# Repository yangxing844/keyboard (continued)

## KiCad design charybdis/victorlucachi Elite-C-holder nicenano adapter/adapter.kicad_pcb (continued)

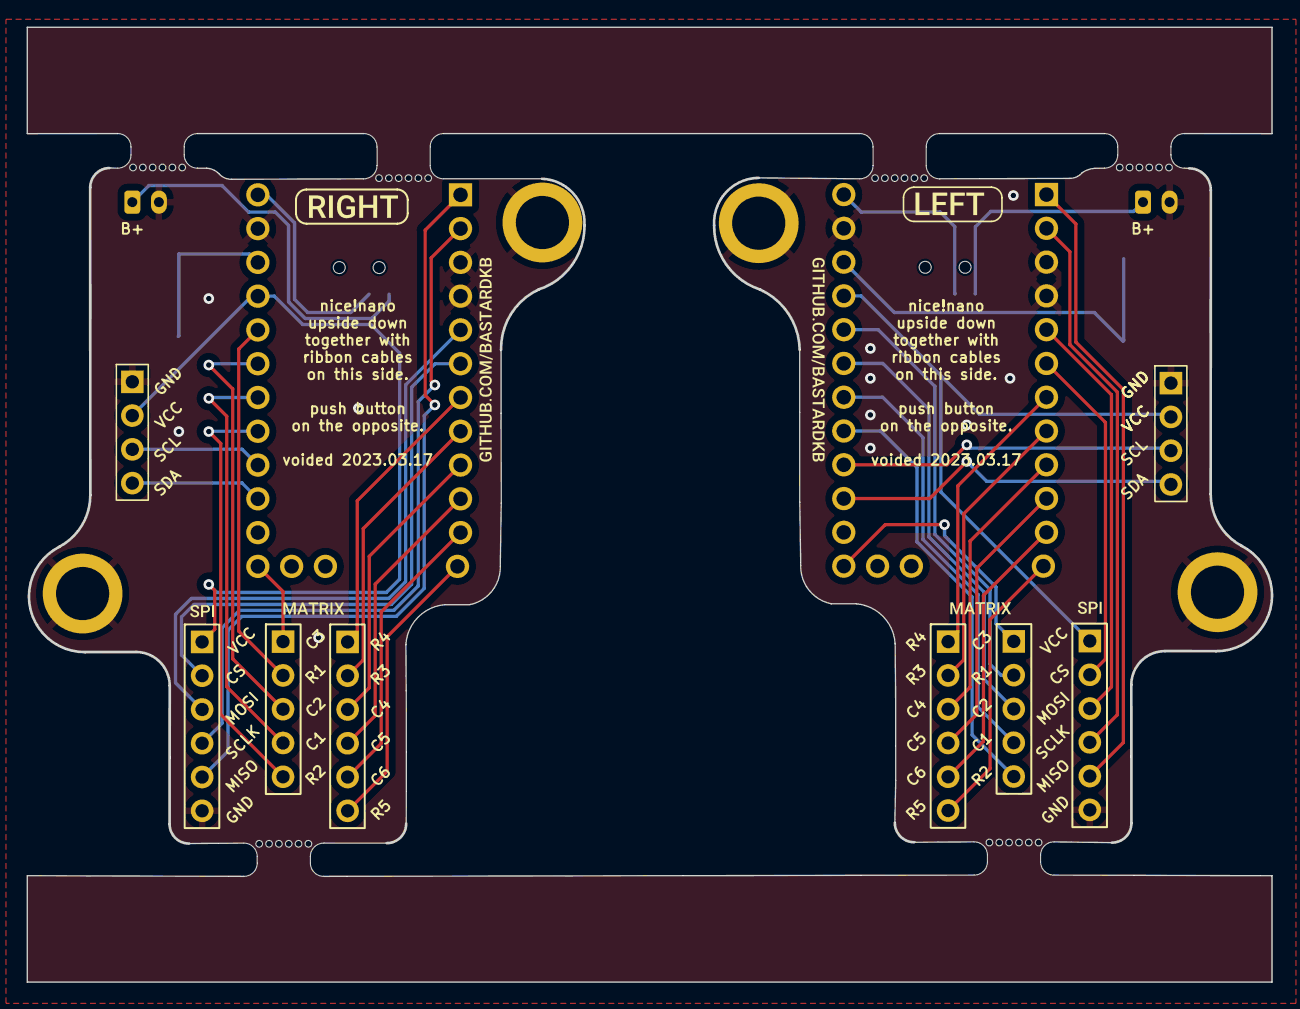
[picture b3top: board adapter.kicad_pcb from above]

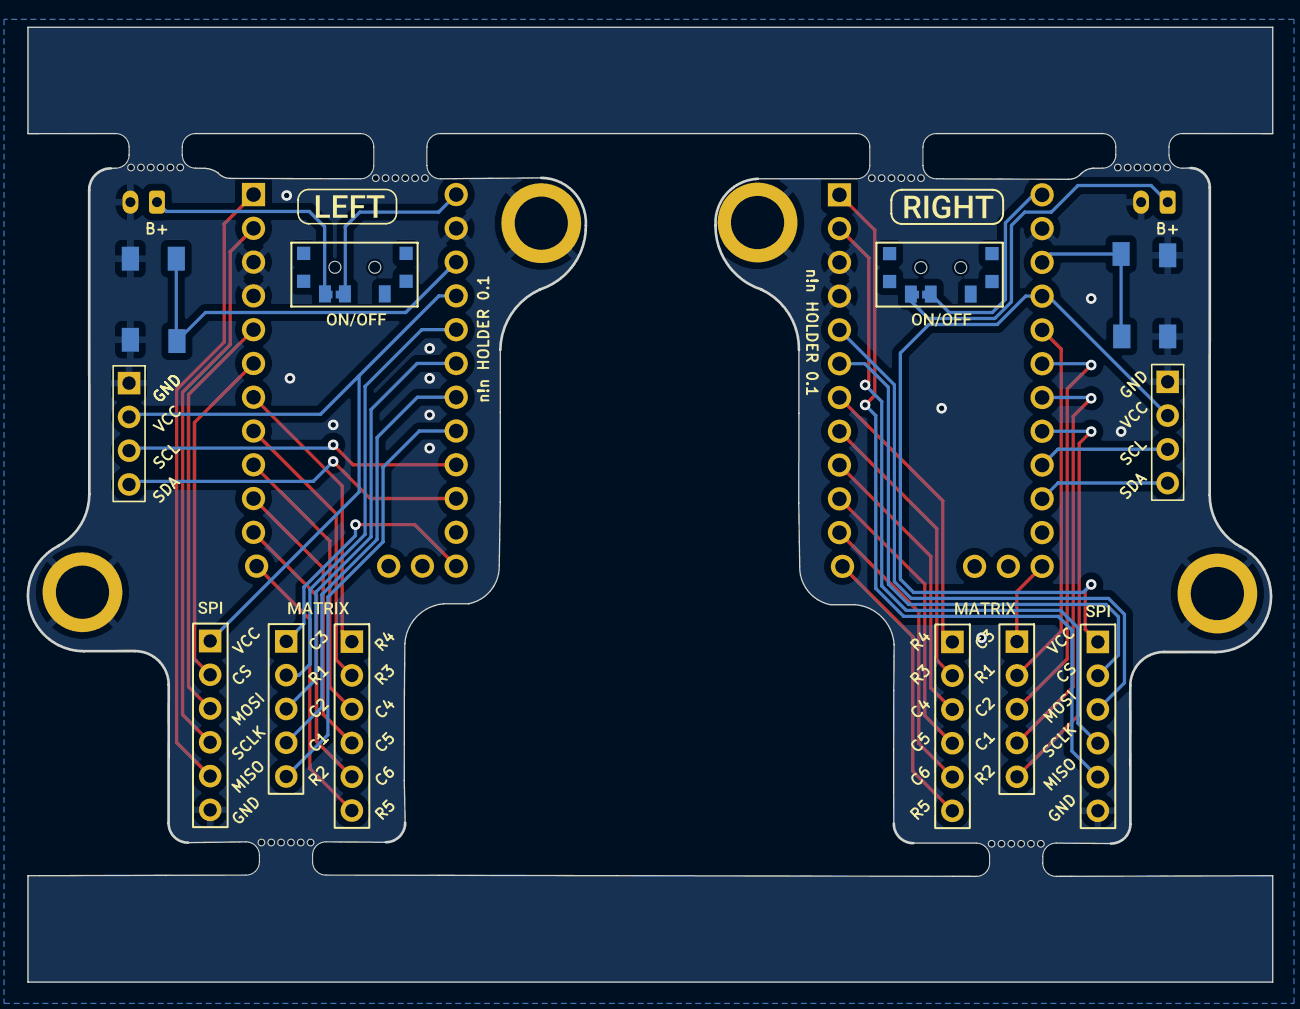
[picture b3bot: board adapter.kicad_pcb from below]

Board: 2 copper layers, 93.6 x 71.8 mm, 38 parts (16 on the bottom side), 42 nets.

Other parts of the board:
kibuzzard-61F01A92, kibuzzard-61F01A92#2: G***; kibuzzard-61F01A92
kibuzzard-61F01B61, kibuzzard-61F01B61#2: G***; kibuzzard-61F01B61
kibuzzard-61F01940, kibuzzard-61F01940#2, kibuzzard-61F01940#3, kibuzzard-61F01940#4: G***; kibuzzard-61F01940
kibuzzard-61F01957, kibuzzard-61F01957#2, kibuzzard-61F01957#3, kibuzzard-61F01957#4: G***; kibuzzard-61F01957
kibuzzard-620B8593, kibuzzard-620B8593#2: G***; kibuzzard-620B8593
kibuzzard-6208EFFE, kibuzzard-6208EFFE#2: G***; kibuzzard-6208EFFE

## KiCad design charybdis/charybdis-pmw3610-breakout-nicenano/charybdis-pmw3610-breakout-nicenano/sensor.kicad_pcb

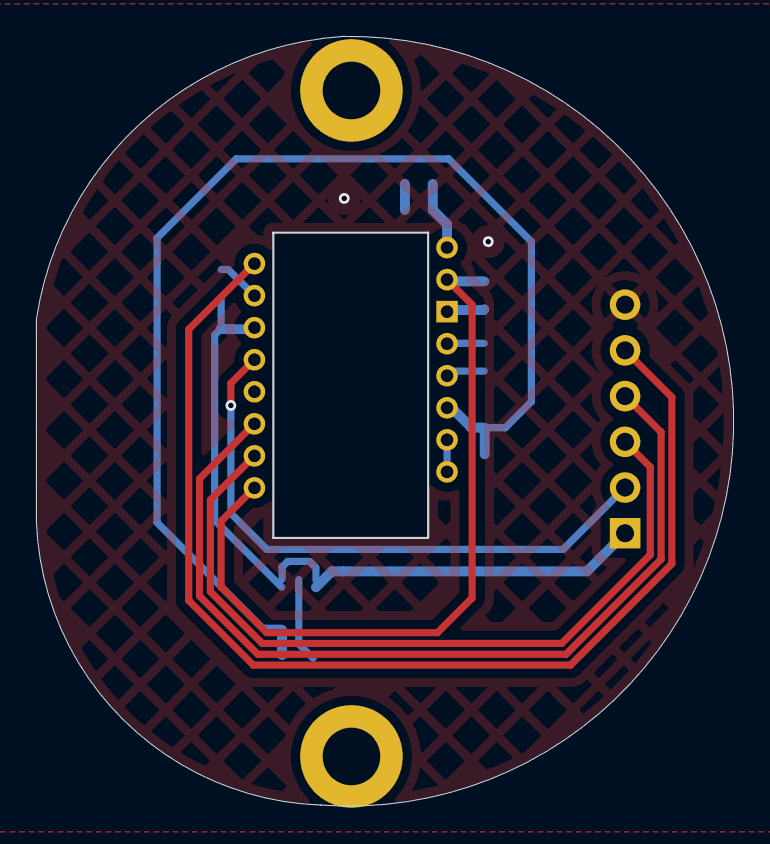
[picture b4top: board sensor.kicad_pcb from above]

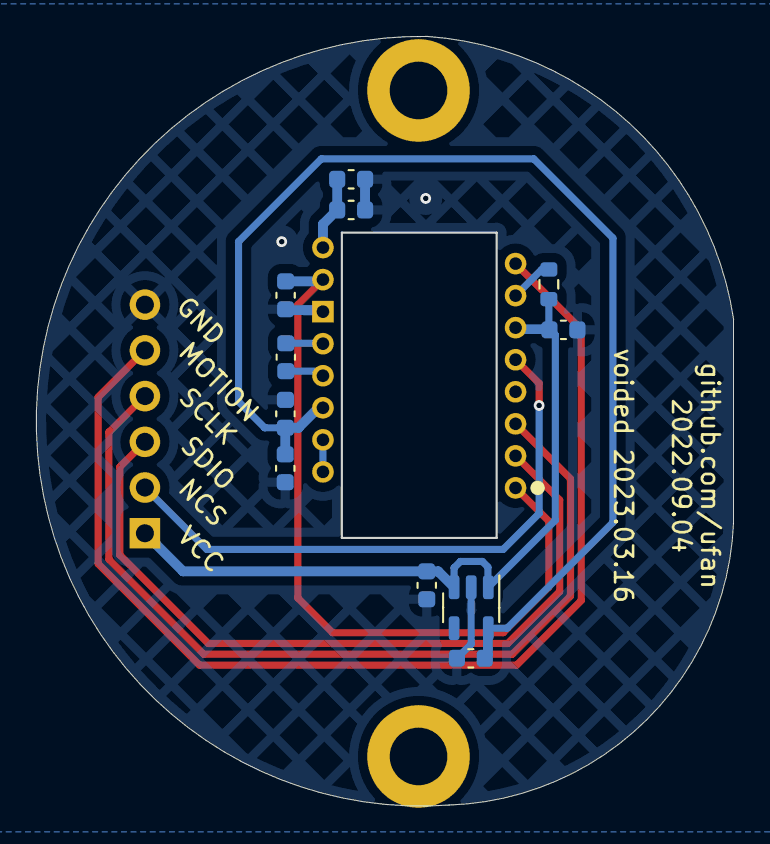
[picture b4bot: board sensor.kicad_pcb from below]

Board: 2 copper layers, 38.7 x 42.8 mm, 15 parts (12 on the bottom side), 13 nets.

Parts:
C1: 10n; C_0603_1608Metric
C2, C7: 100n; C_0603_1608Metric
C3: 3.3u/16V; C_0603_1608Metric
C4: 0.1u; C_0603_1608Metric
C5: 1u; C_0603_1608Metric
C6: 100n (X7R); C_0603_1608Metric
C8: 10u (X7R); C_0603_1608Metric
C9: 10n (X7R); C_0603_1608Metric
H1, H2: MountingHole; MountingHole_3.2mm_M3_ISO7380_Pad
J1: Conn_01x06; PinHeader_1x06_P2.54mm_Vertical
R1: 2M; R_0603_1608Metric
U1: TCR2EF19; SOT-23-5
U2: PMW3610

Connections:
+1V9: C2.1, C3.1, C5.1, U1.5 (OUT), U2.14 (VDD)
GND: C1.2, C2.2, C3.2, C4.1, C5.2, C7.2, C8.2, C9.2, J1.6, U1.2 (GND), U2.11 (GND)
MOTION_2: J1.5, U2.8 (MOTION)
NCS_2: J1.2, U2.5 (NCS)
unnamed: C1.1, U2.1 (+VCSEL), U2.10 (PASS_T)
unnamed: U2.15 (XYLASER), U2.16 (-VCSEL)
unnamed: C6.1, U2.13 (CN)
unnamed: C6.2, U2.12 (CP)
unnamed: R1.1, U2.7 (NRESET)
unnamed: C8.1, C9.1, U2.9 (VCP)
SCLK_2: J1.4, U2.3 (SCLK)
SDIO_2: J1.3, U2.2 (SDIO)
VCC: C4.2, C7.1, J1.1, R1.2, U1.1 (IN), U1.3 (EN), U2.6 (VDDIO)

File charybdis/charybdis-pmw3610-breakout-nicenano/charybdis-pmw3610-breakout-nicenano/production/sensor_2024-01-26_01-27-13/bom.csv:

Designator,Footprint,Quantity,Value,LCSC Part #
C1,0603,1,10n,C19666
"C2, C7",0603,2,100n,C19666
C3,0603,1,3.3u/16V,C19666
C4,0603,1,0.1u,C14663
C5,0603,1,1u,C15849
C6,0603,1, 100n (X7R),C19666
C8,0603,1, 10u (X7R),C19666
C9,0603,1, 10n (X7R),C19666
J1,PinHeader_1x06_P2.54mm_Vertical,1,Conn_01x06,
R1,0603,1,2M,
U1,SOT-23-5,1,TCR2EF19,C146366
U2,PMW3610,1,PMW3610,

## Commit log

2023-10-19 add blender model for all of my 3d print files
2023-10-19 change corne model
2023-10-21 add plate
2023-10-22 I finally know how to add sinks to my switch plate
2023-10-23 switch near done
2023-10-24 level case
2024-02-24 remove corne file
2024-02-29 add corne v4 and wireless charybdis
